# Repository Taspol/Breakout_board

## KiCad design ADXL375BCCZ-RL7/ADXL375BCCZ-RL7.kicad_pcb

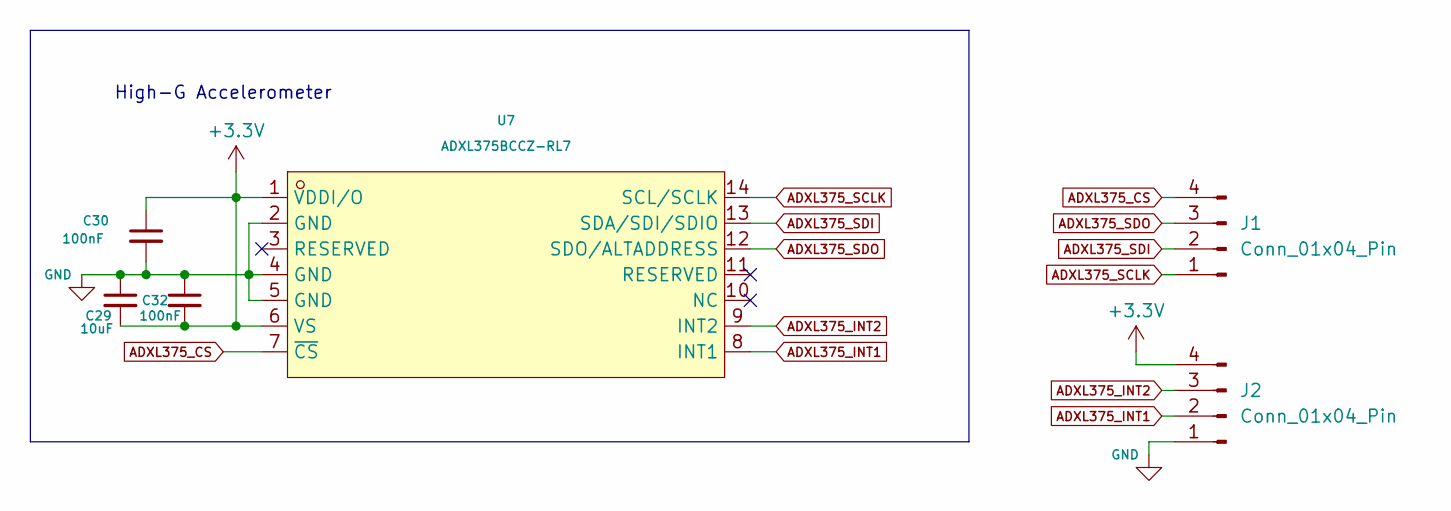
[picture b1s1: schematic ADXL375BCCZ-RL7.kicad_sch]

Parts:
C29: 10uF; C_0805_2012Metric
C30, C32: 100nF; C_0805_2012Metric
J1, J2: Conn_01x04_Pin; PinHeader_1x04_P2.54mm_Vertical
U7: ADXL375BCCZ-RL7; LGA-14_L5.0-W3.0-P0.80-BL; LCSC Part C481898

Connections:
+3.3V: C29.2, C30.1, C32.2, J2.4, U7.1 (VDDI/O), U7.6 (VS)
ADXL375_CS: J1.4, U7.7 (~CS)
ADXL375_INT1: J2.2, U7.8 (INT1)
ADXL375_INT2: J2.3, U7.9 (INT2)
ADXL375_SCLK: J1.1, U7.14 (SCL/SCLK)
ADXL375_SDI: J1.2, U7.13 (SDA/SDI/SDIO)
ADXL375_SDO: J1.3, U7.12 (SDO/ALTADDRESS)
GND: C29.1, C30.2, C32.1, J2.1, U7.2 (GND), U7.4 (GND), U7.5 (GND)

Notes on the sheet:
High-G Accelerometer

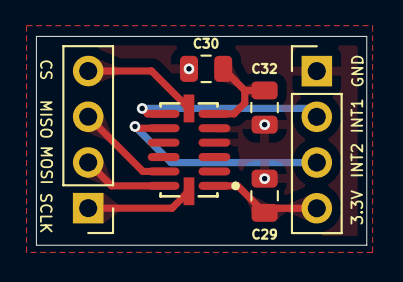
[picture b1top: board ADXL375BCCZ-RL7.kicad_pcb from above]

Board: 2 copper layers, 18.3 x 11.6 mm, 6 parts (0 on the bottom side), 8 nets.

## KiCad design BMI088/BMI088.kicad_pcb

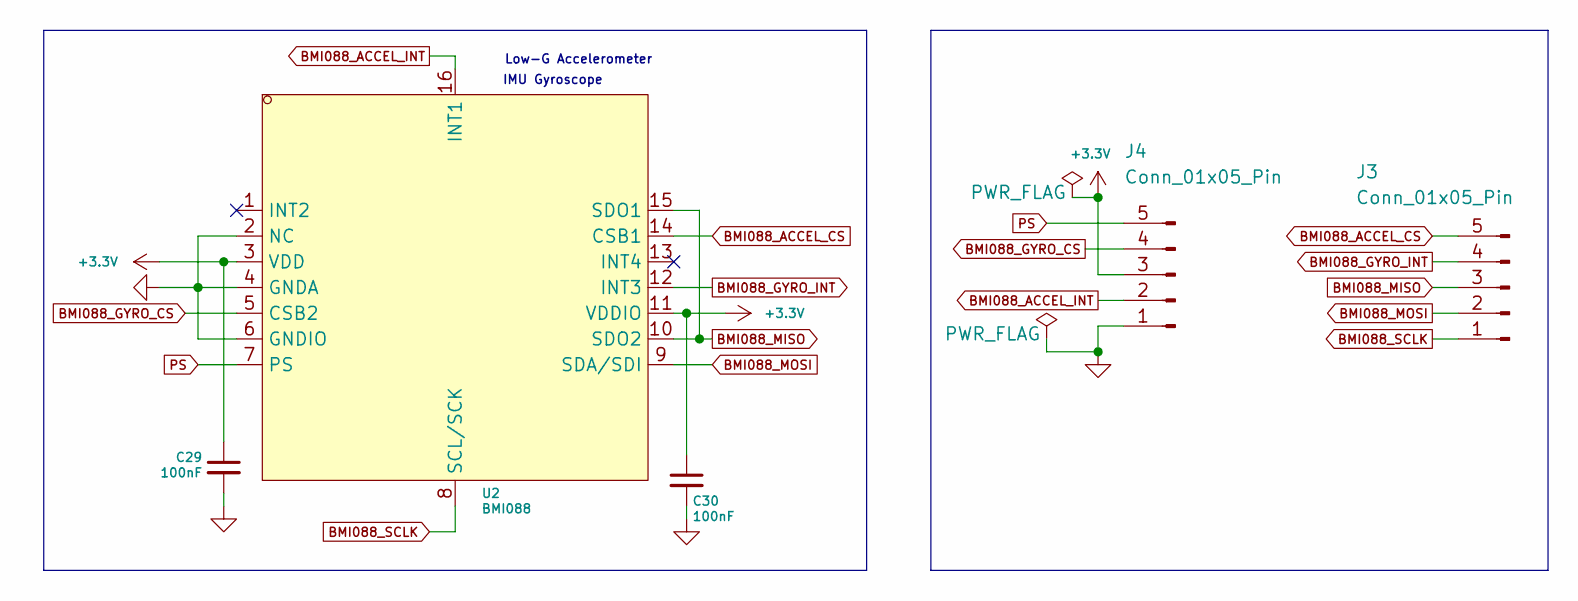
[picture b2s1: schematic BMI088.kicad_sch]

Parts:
C29, C30: 100nF; C_0805_2012Metric_Pad1.18x1.45mm_HandSolder
J3, J4: Conn_01x05_Pin; PinHeader_1x05_P2.54mm_Vertical
U2: BMI088; LGA-16_L4.5-W3.0-P0.50-BL; LCSC Part C194919

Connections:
+3.3V: C29.1, C30.1, J4.3, U2.3 (VDD), U2.11 (VDDIO)
BMI088_ACCEL_CS: J3.5, U2.14 (CSB1)
BMI088_ACCEL_INT: J4.2, U2.16 (INT1)
BMI088_GYRO_CS: J4.4, U2.5 (CSB2)
BMI088_GYRO_INT: J3.4, U2.12 (INT3)
BMI088_MISO: J3.3, U2.10 (SDO2), U2.15 (SDO1)
BMI088_MOSI: J3.2, U2.9 (SDA/SDI)
BMI088_SCLK: J3.1, U2.8 (SCL/SCK)
GND: C29.2, C30.2, J4.1, U2.2 (NC), U2.4 (GNDA), U2.6 (GNDIO)
PS: J4.5, U2.7 (PS)

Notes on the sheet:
IMU Gyroscope
Low-G Accelerometer

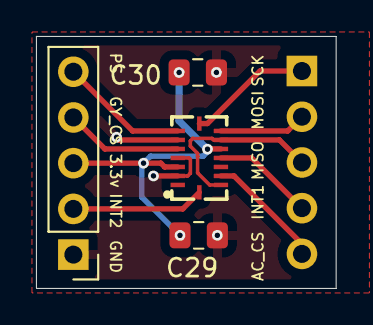
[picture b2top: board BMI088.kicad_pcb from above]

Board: 2 copper layers, 16.7 x 14.0 mm, 5 parts (1 on the bottom side), 10 nets.

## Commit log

2025-04-26 init repo
2025-04-26 add silkscreen
